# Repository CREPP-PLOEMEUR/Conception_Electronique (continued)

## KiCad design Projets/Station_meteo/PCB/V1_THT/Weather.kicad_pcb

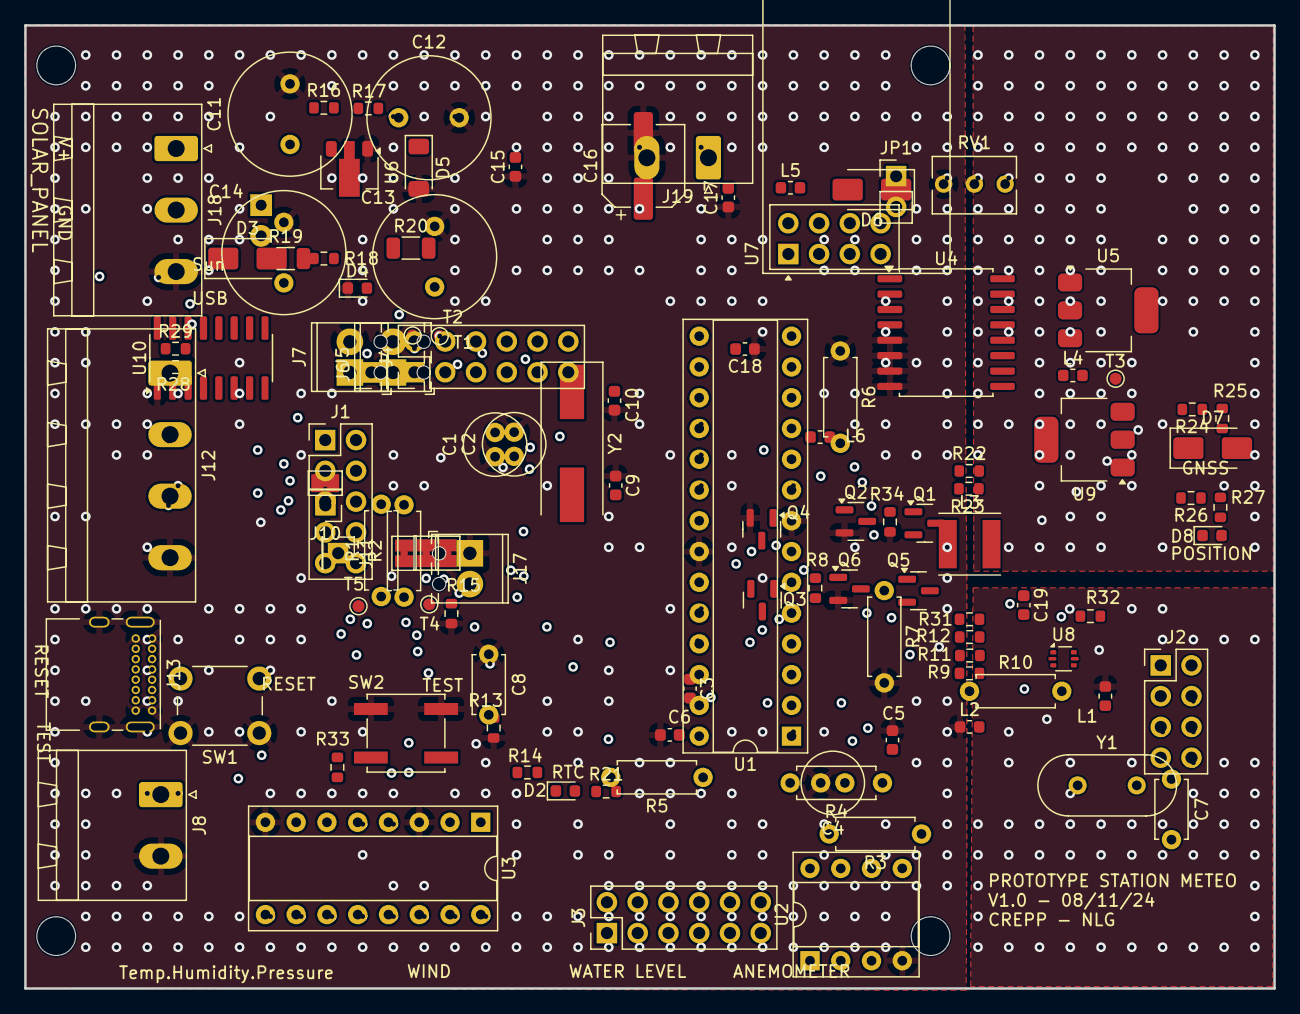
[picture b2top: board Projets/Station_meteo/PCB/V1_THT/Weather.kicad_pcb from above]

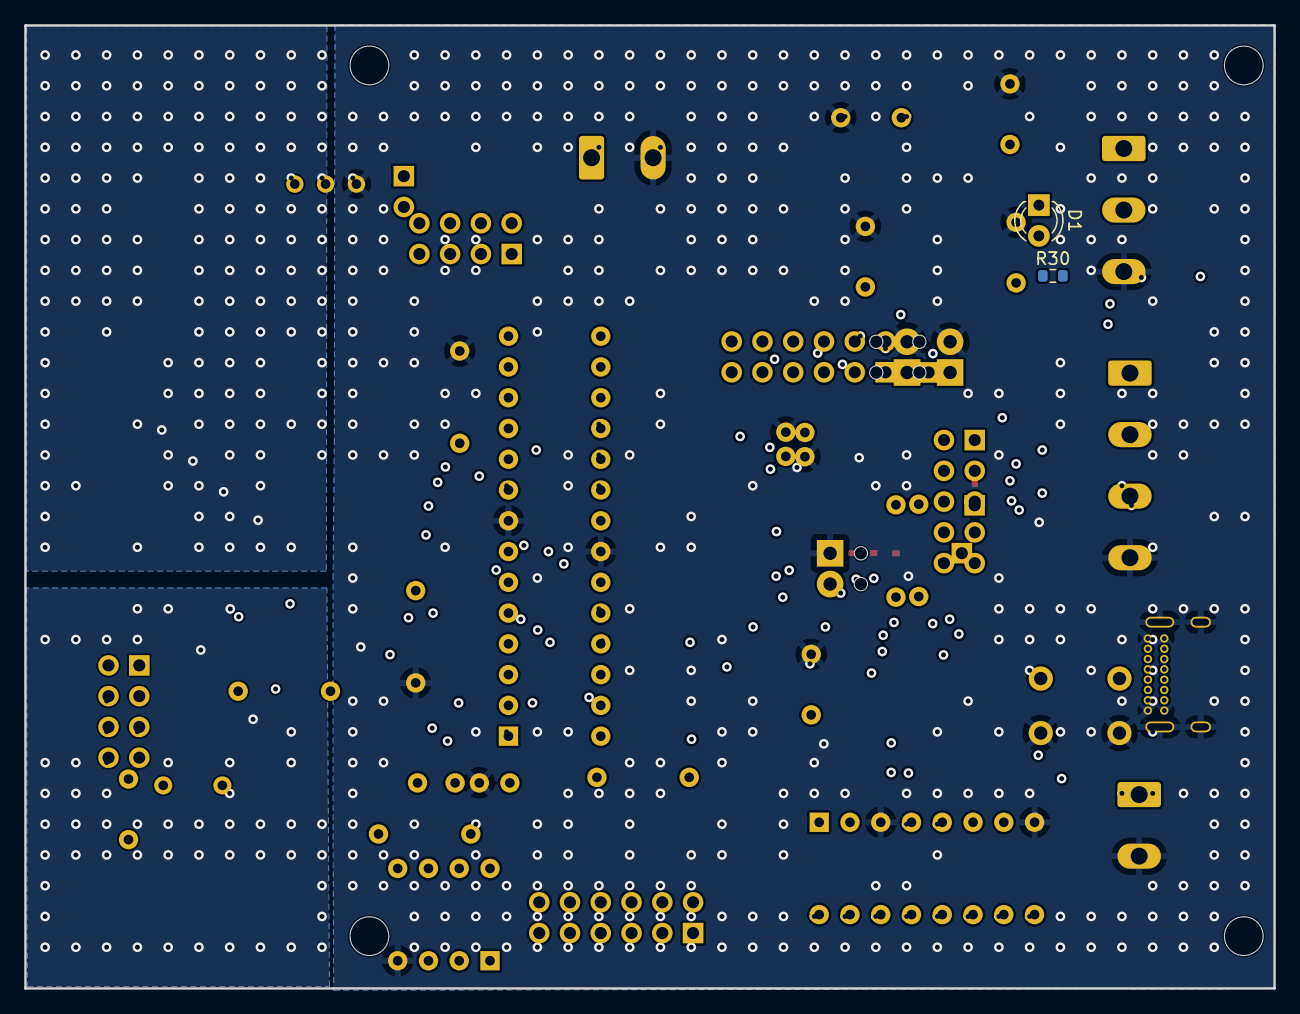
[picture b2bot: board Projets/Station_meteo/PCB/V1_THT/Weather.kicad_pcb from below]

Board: 2 copper layers, 103.1 x 79.5 mm, 117 parts (2 on the bottom side), 96 nets, no tracks yet.

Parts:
C1, C2, C4: 100nF; C_Radial_D5.0mm_H11.0mm_P2.00mm
C3, C5, C6, C19: 100nF; C_0603_1608Metric
C7, C8: 22pF; C_Disc_D4.7mm_W2.5mm_P5.00mm
C9, C10, C17, C18: 2.2uF; C_0603_1608Metric
C11, C12, C13, C14: 5F; C_Radial_D10.0mm_H20.0mm_P5.00mm
C15: 47uF; C_0603_1608Metric
C16: 100uF; CP_Elec_6.3x7.7
D1: LED; LED_D3.0mm
D2: LED; LED_0603_1608Metric
D3, D6, D7: SS24; D_SMA
D4: SUN; LED_0603_1608Metric
D5: D_Zener; D_MiniMELF
D8: LED_USB; LED_0603_1608Metric
H1, H2, H3, H4: MountingHole_Pad; MountingHole_3.2mm_M3
J1: Conn_02x05_Odd_Even; PinHeader_2x05_P2.54mm_Vertical
J2: Conn_02x04_Odd_Even; PinHeader_2x04_P2.54mm_Vertical
J3, J4: Conn_02x06_Odd_Even; PinHeader_2x06_P2.54mm_Vertical
J5: Wind; TerminalBlock_Phoenix_MPT-0,5-2-2.54_1x02_P2.54mm_Horizontal
J6: RAW_data_Wind; PinHeader_1x01_P2.54mm_Vertical
J7: USR_BTN; TerminalBlock_Phoenix_MPT-0,5-2-2.54_1x02_P2.54mm_Horizontal
J8: Panel; PhoenixContact_MSTBA_2,5_2-G-5,08_1x02_P5.08mm_Horizontal
J9, J14, J15, J16: SolderJumper_2_Bridged; SolderJumper-2_P1.3mm_Bridged_Pad1.0x1.5mm
J10, J11: Conn_01x01_Pin; PinHeader_1x01_P2.54mm_Vertical
J12: Screw_Terminal_01x04; PhoenixContact_MSTBA_2,5_4-G-5,08_1x04_P5.08mm_Horizontal
J13: USB_C_Receptacle_USB2.0_16P; USB_C_Receptacle_GCT_USB4085
J17: KF128-2.54_2P; TerminalBlock_Phoenix_MPT-0,5-2-2.54_1x02_P2.54mm_Horizontal
J18: Screw_Terminal_01x03; PhoenixContact_MSTBA_2,5_3-G-5,08_1x03_P5.08mm_Horizontal
J19: Water_Level; PhoenixContact_MSTBA_2,5_2-G-5,08_1x02_P5.08mm_Horizontal
JP1: Jumper; PinHeader_1x02_P2.54mm_Vertical
L1, L2, L4, L5, L6: MPZ1608S101ATAH0; L_0603_1608Metric
L3: 33uH; L_Taiyo-Yuden_NR-50xx
Q1, Q3, Q5: CJ3401; SOT-23
Q2, Q4, Q6: 2N7002H; SOT-23
R1, R2, R3, R4, R5, R6, R10: 10k; R_Axial_DIN0207_L6.3mm_D2.5mm_P7.62mm_Horizontal
R7: 270; R_Axial_DIN0207_L6.3mm_D2.5mm_P7.62mm_Horizontal
R8, R17, R21, R22, R23, R24, R25, R26, R27: 0; R_0603_1608Metric
R9, R18: 330; R_0603_1608Metric
R11, R29, R31, R33: 10k; R_0603_1608Metric
R12, R13, R14, R30, R32, R34: 100k; R_0603_1608Metric
R15: 390; R_0603_1608Metric
R16, R28: 270; R_0603_1608Metric
R19, R20: 100; R_1206_3216Metric
RV1: R_Potentiometer; Potentiometer_Bourns_3266Y_Vertical
SW1: SW_B; SW_PUSH_6mm_H8mm
SW2: PB_SMD_12V_50MA_6MM_6MM; SW_Push_1P1T_NO_CK_KSC7xxJ
T1, T2, T3, T4, T5: TP; TestPoint_Pad_D1.0mm
U1: ATmega328P-P; DIP-28_W7.62mm_Socket
U2: LM358; DIP-8_W7.62mm_Socket
U3: 74HC123; DIP-16_W7.62mm_Socket
U4: DS3231M; SOIC-16W_7.5x10.3mm_P1.27mm
U5: LM317_SOT-223; SOT-223-3_TabPin2
U6: BL8530; SOT-89-3
U7: NRF24L01_Breakout; nRF24L01_Breakout
U8: USBLC6-2P6; SOT-666
U9: AMS1117-3.3; SOT-223-3_TabPin2
U10: CH340G; SOIC-16_3.9x9.9mm_P1.27mm
Y1: 16MHz; Crystal_HC49-4H_Vertical
Y2: 12MHz; Crystal_SMD_HC49-SD

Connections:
/+3.3V_MCU: R10.1, R29.1
/+5V_USB: C17.2, D3.2 (A), J13.A4 (VBUS), J13.A9 (VBUS), J13.B4 (VBUS), J13.B9 (VBUS), U8.5 (VBUS), U9.3 (VI)
/Enable_GNSS: J2.8, Q4.1 (G), R32.1
/Enable_RF: J4.11, Q2.1 (G), R12.1
/Enable_Sensors: J2.6, Q6.1 (G), R34.1
/Interfaces/+3.3V: C6.1, D2.2 (A), J12.1, J18.1, Q5.3 (D), R30.1, U4.2 (VCC), U4.4 (~RST)
/Interfaces/Direction: J3.5, J18.2
/Interfaces/Water_Level: J4.7, J19.1, R30.2
/MCU/+VCC: C1.2, L5.2, U1.7 (VCC), U1.20 (AVCC)
/MCU/CLK: J1.2, R23.1
/MCU/MISO: J1.4, R21.1
/MCU/MOSI: J1.6, R22.1
/MCU/PB0: J2.1, U1.14 (PB0)
/MCU/PB2-D10~: J1.8, R24.1
/MCU/PC0-A0: J3.1, J9.2 (B)
/MCU/PC1-A1: J3.3, R13.1, R14.2
/MCU/PD3-D3-(INT1)~: J4.9, J17.2, R29.2, SW2.2 (B)
/MCU/PD7-D7: J2.4, R25.1
/MCU/RX: J4.3, J15.2 (B)
/MCU/SCL: J3.11, J12.2, U4.16 (SCL)
/MCU/SDA: J3.9, J12.3, U4.15 (SDA)
/MCU/TX: J4.5, J16.2 (B)
/MCU/XTAL1/PB6: C7.2, U1.9 (XTAL1/PB6), Y1.2
/MCU/XTAL2/PB7: C8.2, U1.10 (XTAL2/PB7), Y1.1
/NRF24/+3.3V: L6.1, L6.2, Q1.3 (D), U7.2 (VCC)
/Power/+3.3V: C16.1, D7.1 (K), J10.1, R20.1, U6.2 (OUT)
/Power/+3.3V_RF: J11.1, L4.1, L5.1, Q1.2 (S), Q3.2 (S), R11.2, R20.2, R31.2, T5.1
/Power/+3.3V_Sensors: L4.2, Q5.2 (S), R33.2
/Programming/+3.3V: C18.2, D8.2 (A), J14.2 (B), U9.2 (VO), U10.16 (VCC)
/Programming/D+: U8.1 (I/O1), U10.5 (UD+)
/Programming/D-: U8.3 (I/O2), U10.6 (UD-)
/RESET: C19.2, J4.1, J7.1, R10.2, SW1.2 (B)
/WIND/Vcc: C2.1, C4.1, R1.1, R2.1, RV1.1, U2.8 (V+), U3.16 (VCC)
/WIND/Wind_interrupt: JP1.1 (A), R5.2, R6.2, U2.1
GND: C1.1, C2.2, C4.2, C5.2, C6.2, C7.1, C8.1, C9.1, C10.1, C11.2, C12.2, C13.2, C14.2, C15.1, C16.2, C17.1, C18.1, D4.1 (K), D5.2 (A), J5.2, J7.2, J8.2, J12.4, J13.A1 (GND), J13.A12 (GND), J13.B1 (GND), J13.B12 (GND), J13.S1 (SHIELD), J17.1, J18.3, J19.2, L1.1, L2.1, Q2.2 (S), Q4.2 (S), Q6.2 (S), R6.1, R7.2, R12.2, R13.2, R15.1, R28.2, R32.2, R34.2, RV1.3, SW1.1 (A), SW2.1 (A), U1.8 (GND), U1.22 (GND), U2.4 (V-), U3.3 (Clr), U3.8 (GND), U4.5 (GND), U4.6 (GND), U4.7 (GND), U4.8 (GND), U4.9 (GND), U4.10 (GND), U4.11 (GND), U4.12 (GND), U4.13 (GND), U6.1 (GND), U8.2 (GND), U9.1 (GND), U10.1 (GND)
GND_RF: L1.2, U7.1 (GND)
unnamed: D1.2 (A), JP1.2 (B)
unnamed: D1.1 (K), R7.1
unnamed: D2.1 (K), R9.1
unnamed: C9.2, D3.1 (K), J8.1, R14.1, T2.1, U5.3 (VI)
unnamed: D4.2 (A), R18.1
unnamed: C10.2, D5.1 (K), R16.2, R17.2, R19.1, T3.1, U5.2 (VO)
unnamed: D6.2 (A), R19.2
unnamed: C11.1, C12.1, C13.1, C14.1, C15.2, D6.1 (K), J9.1 (A), L3.1, T4.1
unnamed: D7.2 (A), L3.2, U6.3 (LX)
unnamed: D8.1 (K), R28.1
unnamed: J1.1, U1.19 (PB5)
unnamed: J1.3, U1.18 (PB4)
unnamed: J1.5, U1.17 (PB3)
unnamed: J1.7, U1.16 (PB2)
unnamed: J1.9, U1.15 (PB1)
unnamed: J2.3, U1.13 (PD7)
unnamed: J2.5, U1.12 (PD6)
unnamed: J2.7, U1.11 (PD5)
unnamed: J3.2, U1.23 (PC0)
unnamed: J3.4, U1.24 (PC1)
unnamed: J3.6, U1.25 (PC2)
unnamed: J3.8, U1.26 (PC3)
unnamed: J3.10, U1.27 (PC4)
unnamed: J3.12, U1.28 (PC5)
unnamed: J4.2, U1.1 (~RESET/PC6)
unnamed: J4.4, U1.2 (PD0)
unnamed: J4.6, U1.3 (PD1)
unnamed: J4.8, U1.4 (PD2)
unnamed: J4.10, U1.5 (PD3)
unnamed: J4.12, U1.6 (PD4)
unnamed: J5.1, J6.1, R1.2, U3.2 (B)
unnamed: J13.A6 (D+), J13.B6 (D+), R27.1
unnamed: J13.A7 (D-), J13.B7 (D-), R26.1
unnamed: J14.1 (A), U10.4 (V3)
unnamed: J15.1 (A), U10.2 (TXD)
unnamed: J16.1 (A), U10.3 (RXD)
unnamed: Q1.1 (G), Q2.3 (D), R11.1
unnamed: Q3.1 (G), Q4.3 (D), R31.1
unnamed: Q5.1 (G), Q6.3 (D), R33.1
unnamed: R8.2, R9.2
unnamed: R17.1, R18.2
unnamed: R26.2, U8.4 (I/O2)
unnamed: R27.2, U8.6 (I/O1)
unnamed: R4.2, R5.1, U2.3 (+)
unnamed: RV1.2, U2.2 (-)
unnamed: C5.1, R3.2, U2.5 (+)
unnamed: R4.1, U2.6 (-), U2.7
unnamed: C3.2, U3.14 (Cext)
unnamed: R3.1, U3.13 (Q)
unnamed: C3.1, R2.2, U3.15 (RCext)
unnamed: R8.1, T1.1, U4.3 (~INT/SQW)
unnamed: R15.2, R16.1, U5.1 (ADJ)
unnamed: R25.2, U7.3 (CE)
unnamed: R22.2, U7.7 (MISO)
unnamed: R21.2, U7.6 (MOSI)
unnamed: R23.2, U7.5 (SCK)
unnamed: R24.2, U7.4 (~CSN)
unnamed: U10.7 (XI), Y2.1
unnamed: U10.8 (XO), Y2.2
unnamed: C19.1, U10.13 (~DTR)

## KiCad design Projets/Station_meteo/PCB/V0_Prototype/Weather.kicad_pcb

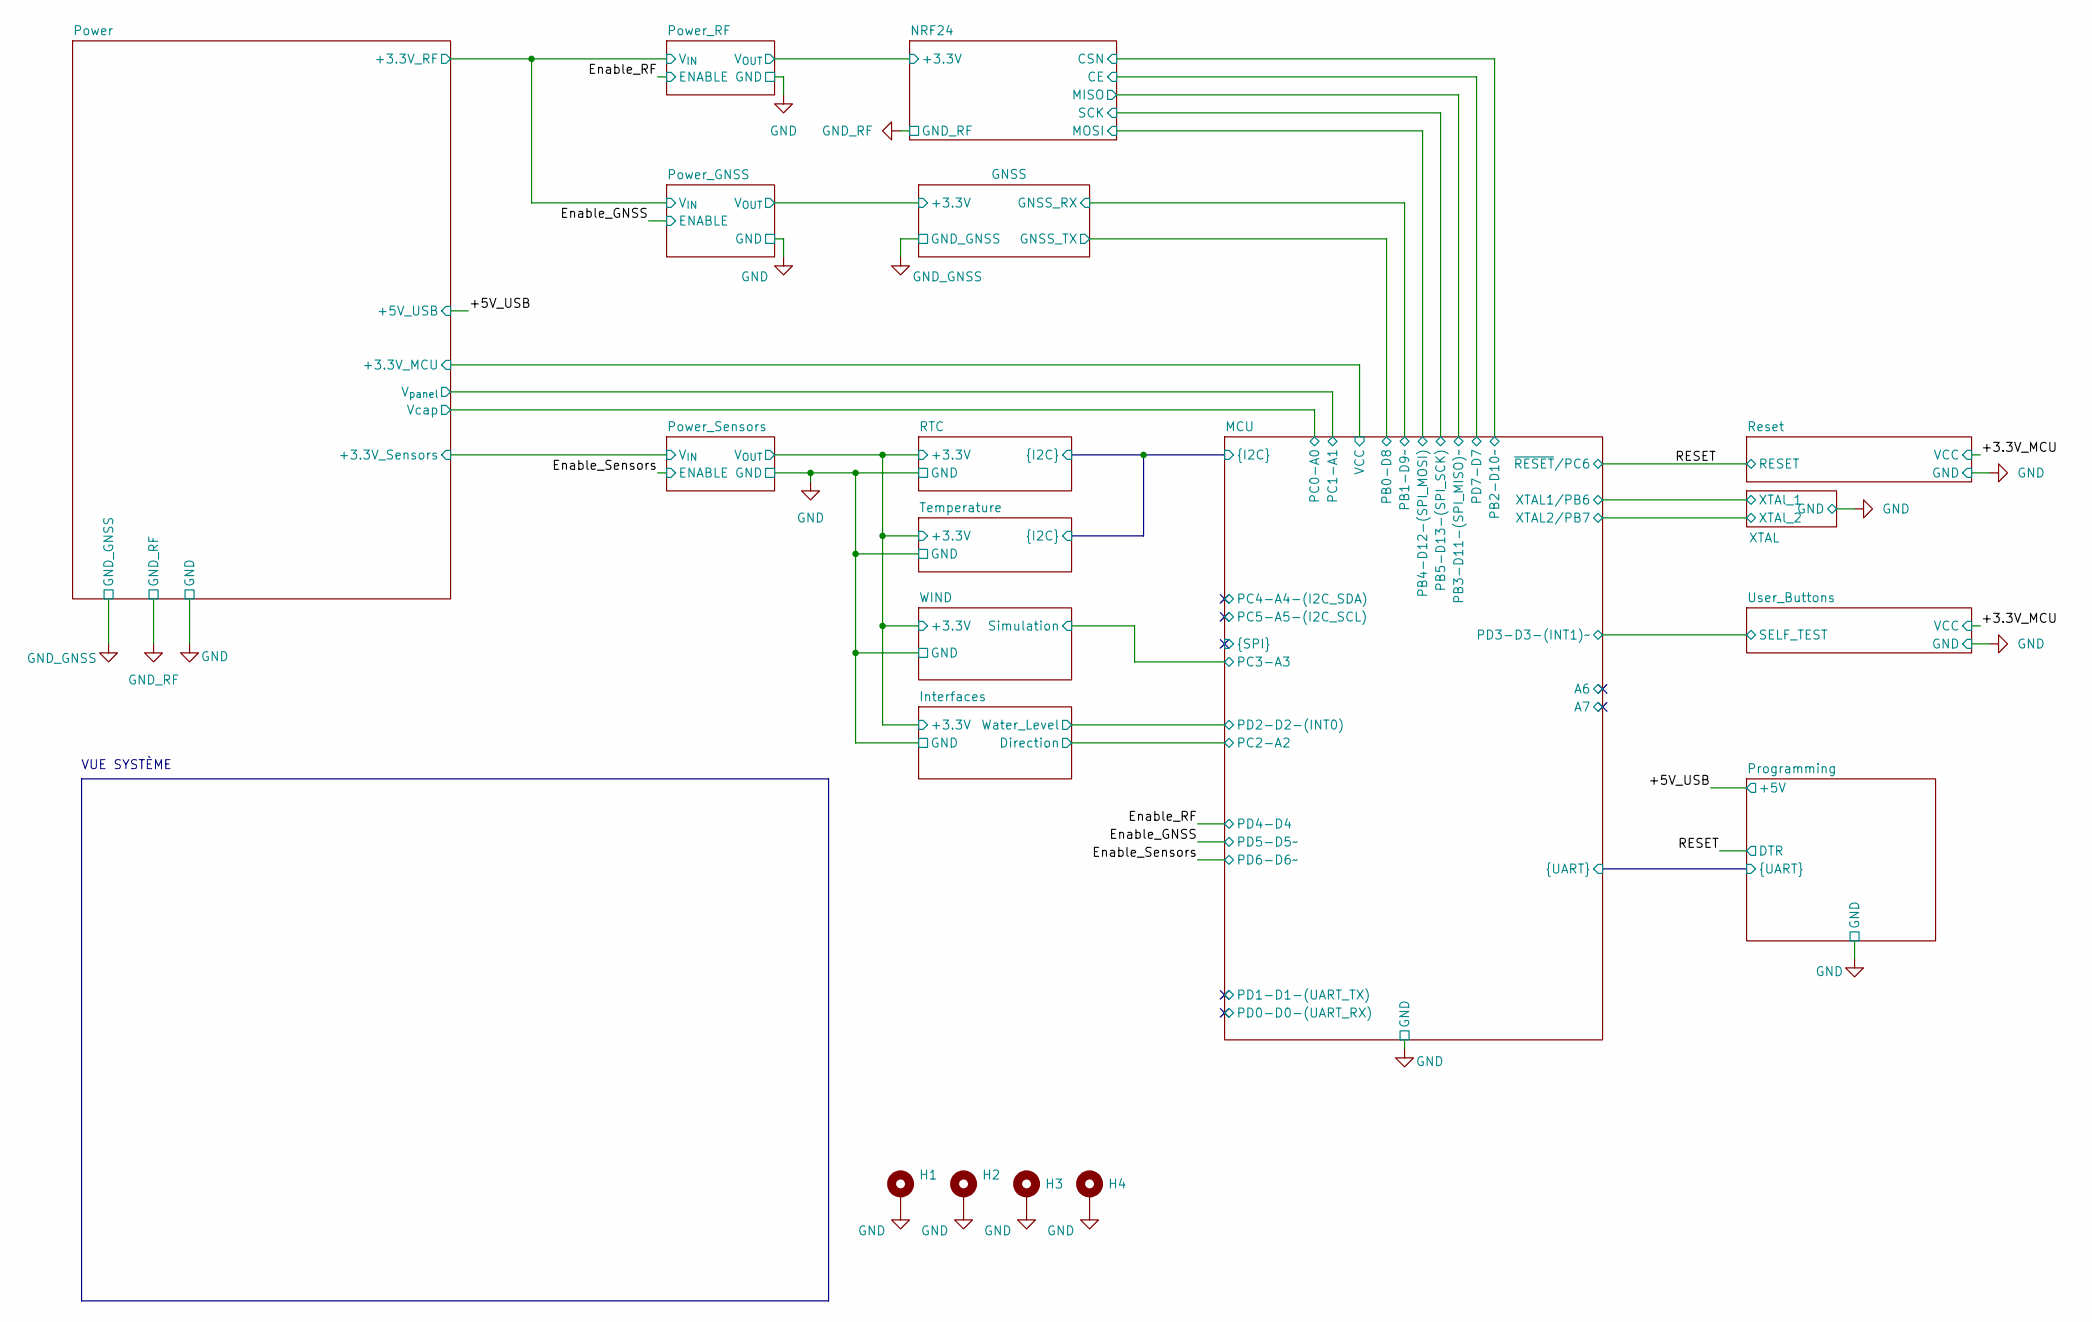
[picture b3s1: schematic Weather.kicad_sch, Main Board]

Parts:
H1, H2, H3, H4: MountingHole_Pad; MountingHole_3.2mm_M3

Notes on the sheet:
VUE SYSTÈME

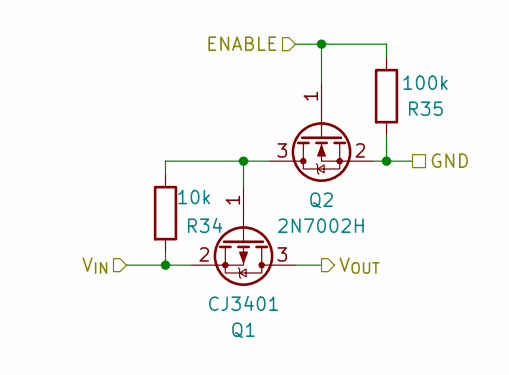
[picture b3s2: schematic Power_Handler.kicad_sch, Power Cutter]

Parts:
Q1: CJ3401; SOT-23
Q2: 2N7002H; SOT-23
R34: 10k; R_0603_1608Metric
R35: 100k; R_0603_1608Metric

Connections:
/Enable_GNSS: Q2.1 (G), R35.1; also elsewhere on the board
/GNSS/+3.3V: Q1.3 (D); also elsewhere on the board
/Power/+3.3V_RF: Q1.2 (S), R34.2; also elsewhere on the board
GND: Q2.2 (S), R35.2; also elsewhere on the board
unnamed: Q1.1 (G), Q2.3 (D), R34.1

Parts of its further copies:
Q3, Q5: CJ3401; SOT-23
Q4, Q6: 2N7002H; SOT-23
R7, R36: 10k; R_0603_1608Metric
R8, R37: 100k; R_0603_1608Metric

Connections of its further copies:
/Enable_RF: Q6.1 (G), R8.1; also elsewhere on the board
/Enable_Sensors: Q4.1 (G), R37.1; also elsewhere on the board
/Interfaces/+3.3V: Q3.3 (D); also elsewhere on the board
/NRF24/+3.3V: Q5.3 (D); also elsewhere on the board
/Power/+3.3V_RF: Q5.2 (S), R7.2; also elsewhere on the board
/Power/+3.3V_Sensors: Q3.2 (S), R36.2; also elsewhere on the board
GND: Q4.2 (S), Q6.2 (S), R8.2, R37.2; also elsewhere on the board
unnamed: Q3.1 (G), Q4.3 (D), R36.1
unnamed: Q5.1 (G), Q6.3 (D), R7.1

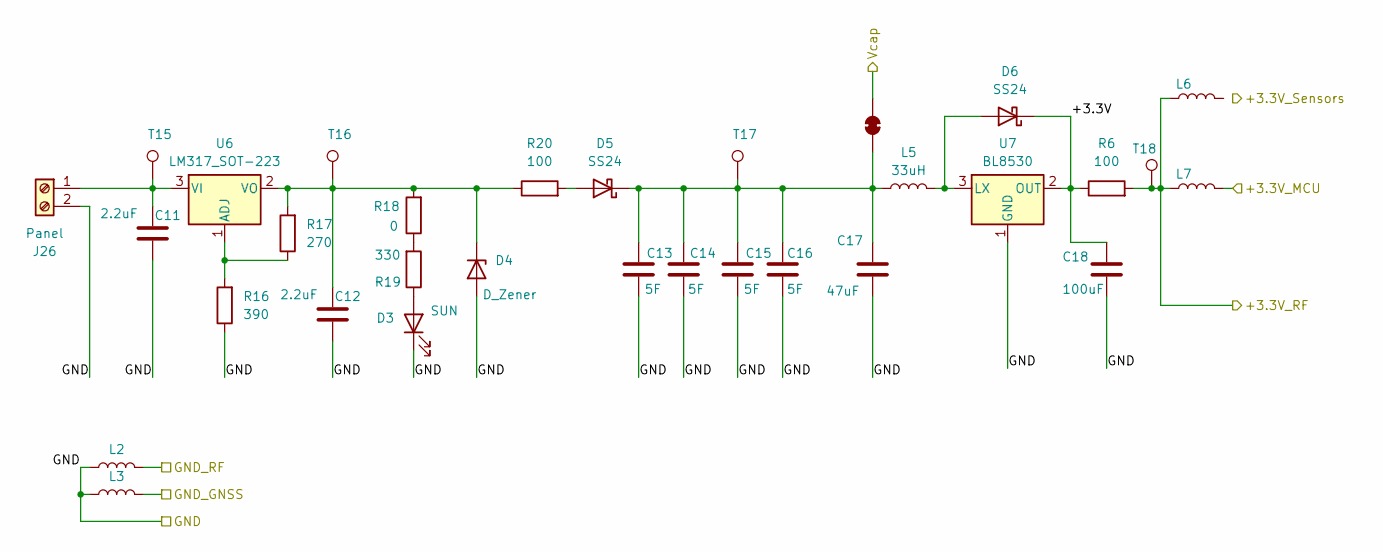
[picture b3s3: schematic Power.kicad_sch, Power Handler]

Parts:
C11, C12: 2.2uF; C_0603_1608Metric
C13, C14, C15, C16: 5F; C_Radial_D10.0mm_H20.0mm_P5.00mm
C17: 47uF; C_0603_1608Metric
C18: 100uF; CP_Elec_6.3x7.7
D3: SUN; LED_0603_1608Metric
D4: D_Zener; D_MiniMELF
D5, D6: SS24; D_SMA
J26: Panel; PhoenixContact_MSTBA_2,5_2-G-5,08_1x02_P5.08mm_Horizontal
J39: SolderJumper_2_Bridged; SolderJumper-2_P1.3mm_Bridged_Pad1.0x1.5mm
L2, L3, L6, L7: MPZ1608S101ATAH0; L_0603_1608Metric
L5: 33uH; L_Taiyo-Yuden_NR-50xx
R6, R20: 100; R_1206_3216Metric
R16: 390; R_0603_1608Metric
R17: 270; R_0603_1608Metric
R18: 0; R_0603_1608Metric
R19: 330; R_0603_1608Metric
T15, T16, T17, T18: TP; TestPoint_Pad_D1.0mm
U6: LM317_SOT-223; SOT-223-3_TabPin2
U7: BL8530; SOT-89-3

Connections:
/MCU/+VCC: L7.2; also elsewhere on the board
/MCU/PC0-A0: J39.2 (B); also elsewhere on the board
/Power/+3.3V: C18.1, D6.1 (K), R6.1, U7.2 (OUT); also elsewhere on the board
/Power/+3.3V_RF: L6.1, L7.1, R6.2, T18.1; also elsewhere on the board
/Power/+3.3V_Sensors: L6.2; also elsewhere on the board
GND: C11.1, C12.1, C13.2, C14.2, C15.2, C16.2, C17.1, C18.2, D3.1 (K), D4.2 (A), J26.2, L2.1, L3.1, R16.1, U7.1 (GND); also elsewhere on the board
GND_GNSS: L3.2; also elsewhere on the board
GND_RF: L2.2; also elsewhere on the board
unnamed 44: C11.2, J26.1, T15.1, U6.3 (VI); also elsewhere on the board
unnamed: D3.2 (A), R19.1
unnamed: C12.2, D4.1 (K), R17.2, R18.2, R20.1, T16.1, U6.2 (VO)
unnamed: D5.2 (A), R20.2
unnamed: C13.1, C14.1, C15.1, C16.1, C17.2, D5.1 (K), J39.1 (A), L5.1, T17.1
unnamed: D6.2 (A), L5.2, U7.3 (LX)
unnamed: R18.1, R19.2
unnamed: R16.2, R17.1, U6.1 (ADJ)

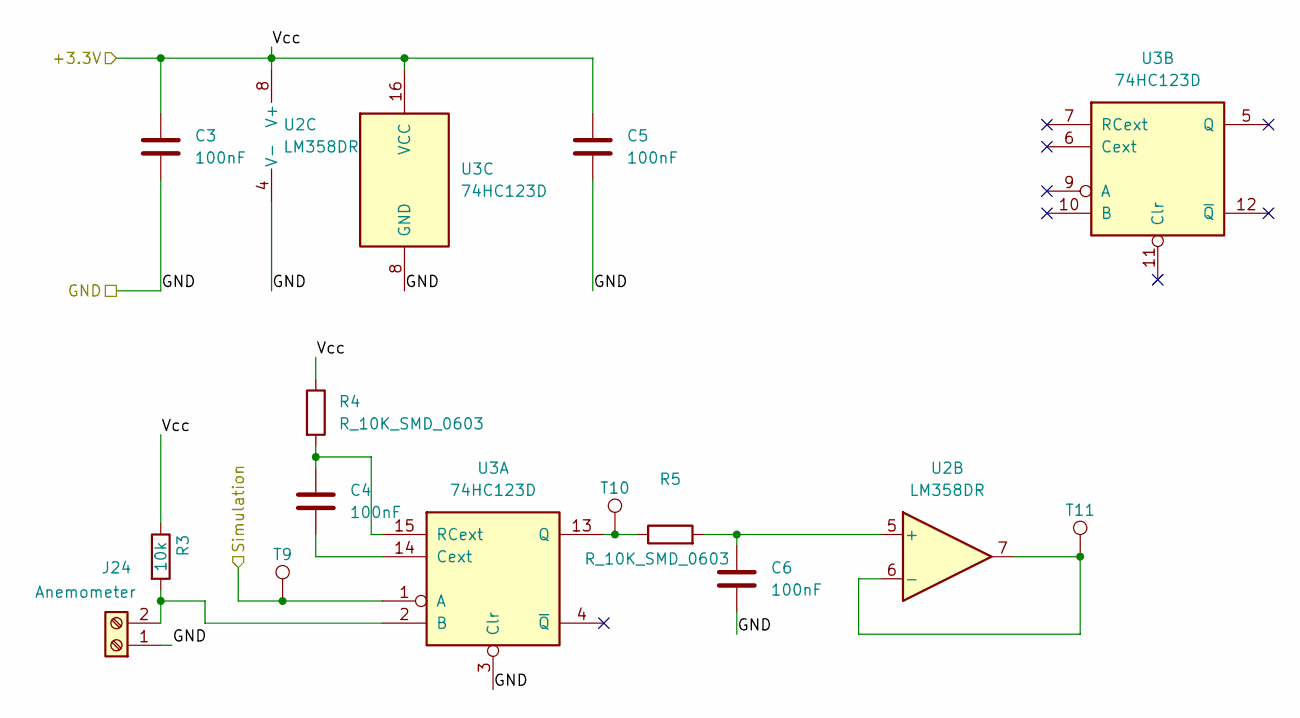
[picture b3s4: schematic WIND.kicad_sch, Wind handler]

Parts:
C3, C4, C5, C6: 100nF; C_0603_1608Metric
J24: Anemometer; PhoenixContact_MSTBA_2,5_2-G-5,08_1x02_P5.08mm_Horizontal
R3: 10k; R_0603_1608Metric
R4, R5: R_10K_SMD_0603; R_0603_1608Metric
T9, T10, T11: TP; TestPoint_Pad_D1.0mm
U2: LM358DR; TSSOP-8_4.4x3mm_P0.65mm
U3: 74HC123D; SOIC-16W_5.3x10.2mm_P1.27mm

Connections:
/Interfaces/+3.3V: C3.1, C5.1, R3.1, R4.1, U2.8 (V+), U3.16 (VCC); also elsewhere on the board
/MCU/PC3-A3: T9.1, U3.1 (A); also elsewhere on the board
GND: C3.2, C5.2, C6.2, J24.1, U2.4 (V-), U3.3 (Clr), U3.8 (GND); also elsewhere on the board
unnamed: J24.2, R3.2, U3.2 (B)
unnamed: C6.1, R5.2, U2.5 (+)
unnamed: T11.1, U2.6 (-), U2.7
unnamed: C4.2, U3.14 (Cext)
unnamed: R5.1, T10.1, U3.13 (Q)
unnamed: C4.1, R4.2, U3.15 (RCext)

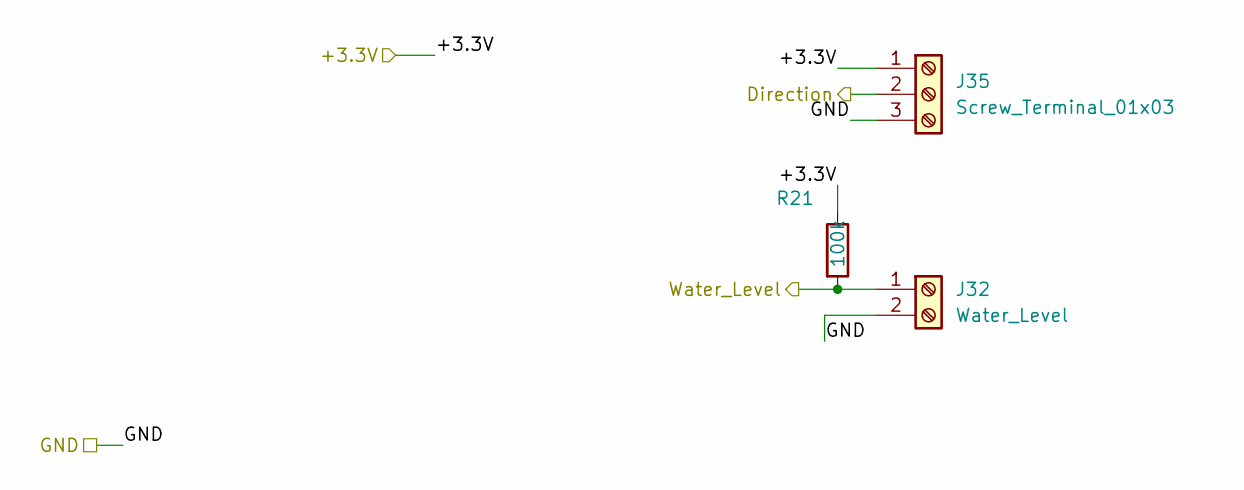
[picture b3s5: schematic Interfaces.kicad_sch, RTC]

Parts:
J32: Water_Level; PhoenixContact_MSTBA_2,5_2-G-5,08_1x02_P5.08mm_Horizontal
J35: Screw_Terminal_01x03; PhoenixContact_MSTBA_2,5_3-G-5,08_1x03_P5.08mm_Horizontal
R21: 100k; R_0603_1608Metric

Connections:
/Interfaces/+3.3V: J35.1, R21.1; also elsewhere on the board
/Interfaces/Direction: J35.2; also elsewhere on the board
/Interfaces/Water_Level: J32.1, R21.2; also elsewhere on the board
GND: J32.2, J35.3; also elsewhere on the board

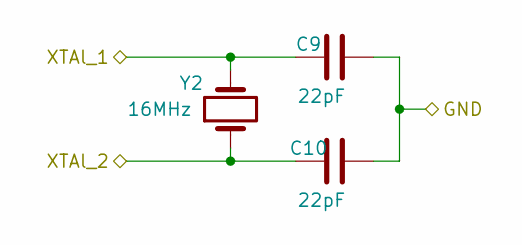
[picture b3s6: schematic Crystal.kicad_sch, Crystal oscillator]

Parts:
C9, C10: 22pF; C_0603_1608Metric
Y2: 16MHz; Crystal_SMD_HC49-SD

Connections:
/MCU/XTAL1/PB6: C9.2, Y2.2; also elsewhere on the board
/MCU/XTAL2/PB7: C10.2, Y2.1; also elsewhere on the board
GND: C9.1, C10.1; also elsewhere on the board

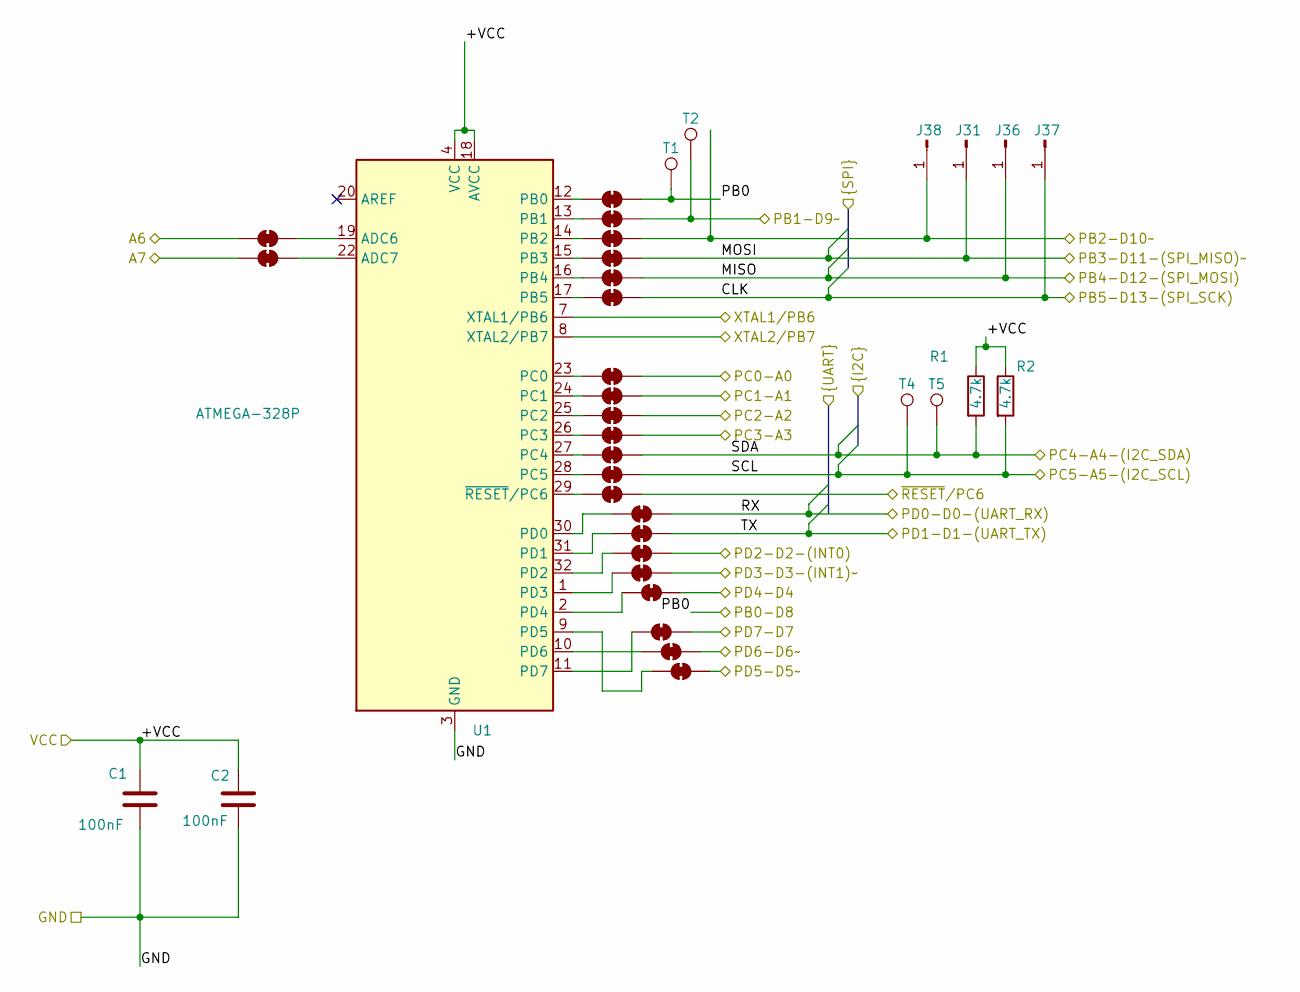
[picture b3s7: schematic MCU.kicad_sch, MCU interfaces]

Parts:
C1, C2: 100nF; C_0603_1608Metric
J1, J2, J3, J4, J5, J6, J7, J8, J9, J10, J11, J12, J13, J14, J15, J16, J17, J18, J19, J20, J21, J22, J23: SolderJumper_2_Bridged; SolderJumper-2_P1.3mm_Bridged_Pad1.0x1.5mm
J31, J36, J37, J38: Conn_01x01_Pin; PinHeader_1x01_P2.54mm_Vertical
R1, R2: 4.7k; R_0603_1608Metric
T1, T2, T4, T5: TP; TestPoint_Pad_D1.0mm
U1: ATMEGA-328P; TQFP-32_7x7mm_P0.8mm

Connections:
/Enable_GNSS: J23.2 (B); also elsewhere on the board
/Enable_RF: J20.2 (B); also elsewhere on the board
/Enable_Sensors: J22.2 (B); also elsewhere on the board
/GNSS/GNSS_RX: J4.2 (B), T2.1; also elsewhere on the board
/Interfaces/Direction: J11.2 (B); also elsewhere on the board
/Interfaces/Water_Level: J18.2 (B); also elsewhere on the board
/MCU/+VCC: C1.2, C2.2, R1.1, R2.1, U1.4 (VCC), U1.6 (VCC), U1.18 (AVCC); also elsewhere on the board
/MCU/A6: J1.1 (A)
/MCU/A7: J2.1 (A)
/MCU/CLK: J8.2 (B), J37.1; also elsewhere on the board
/MCU/MISO: J7.2 (B), J36.1; also elsewhere on the board
/MCU/MOSI: J6.2 (B), J31.1; also elsewhere on the board
/MCU/PB0: J3.2 (B), T1.1; also elsewhere on the board
/MCU/PB2-D10~: J5.2 (B), J38.1; also elsewhere on the board
/MCU/PC0-A0: J9.2 (B); also elsewhere on the board
/MCU/PC1-A1: J10.2 (B); also elsewhere on the board
/MCU/PC3-A3: J12.2 (B); also elsewhere on the board
/MCU/PD3-D3-(INT1)~: J19.2 (B); also elsewhere on the board
/MCU/PD7-D7: J21.2 (B); also elsewhere on the board
/MCU/RX: J16.2 (B); also elsewhere on the board
/MCU/SCL: J14.2 (B), R2.2, T4.1; also elsewhere on the board
/MCU/SDA: J13.2 (B), R1.2, T5.1; also elsewhere on the board
/MCU/TX: J17.2 (B); also elsewhere on the board
/MCU/XTAL1/PB6: U1.7 (XTAL1/PB6); also elsewhere on the board
/MCU/XTAL2/PB7: U1.8 (XTAL2/PB7); also elsewhere on the board
/RESET: J15.2 (B); also elsewhere on the board
GND: C1.1, C2.1, U1.3 (GND), U1.5 (GND), U1.21 (GND); also elsewhere on the board
unnamed: J1.2 (B), U1.19 (ADC6)
unnamed: J2.2 (B), U1.22 (ADC7)
unnamed: J3.1 (A), U1.12 (PB0)
unnamed: J4.1 (A), U1.13 (PB1)
unnamed: J5.1 (A), U1.14 (PB2)
unnamed: J6.1 (A), U1.15 (PB3)
unnamed: J7.1 (A), U1.16 (PB4)
unnamed: J8.1 (A), U1.17 (PB5)
unnamed: J9.1 (A), U1.23 (PC0)
unnamed: J10.1 (A), U1.24 (PC1)
unnamed: J11.1 (A), U1.25 (PC2)
unnamed: J12.1 (A), U1.26 (PC3)
unnamed: J13.1 (A), U1.27 (PC4)
unnamed: J14.1 (A), U1.28 (PC5)
unnamed: J15.1 (A), U1.29 (~RESET/PC6)
unnamed: J16.1 (A), U1.30 (PD0)
unnamed: J17.1 (A), U1.31 (PD1)
unnamed: J18.1 (A), U1.32 (PD2)
unnamed: J19.1 (A), U1.1 (PD3)
unnamed: J20.1 (A), U1.2 (PD4)
unnamed: J21.1 (A), U1.11 (PD7)
unnamed: J22.1 (A), U1.10 (PD6)
unnamed: J23.1 (A), U1.9 (PD5)

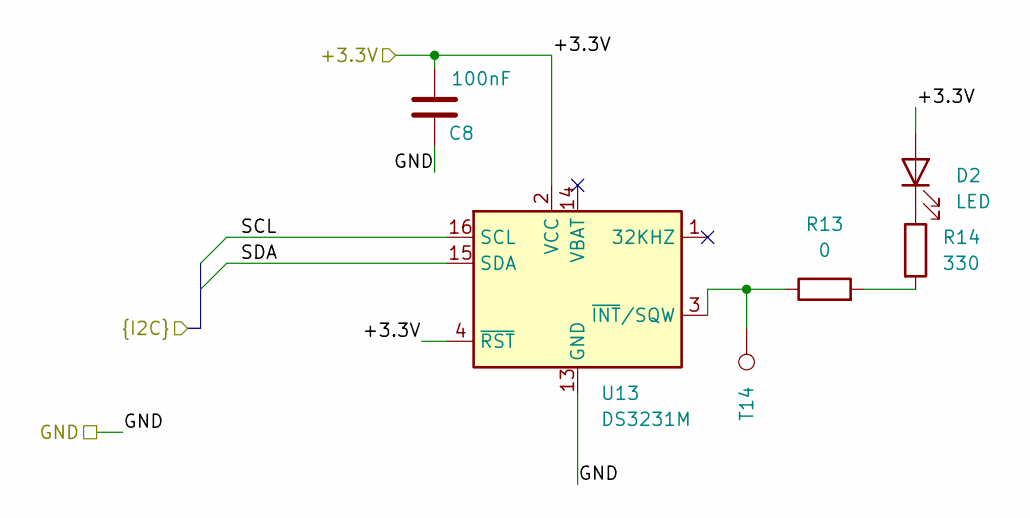
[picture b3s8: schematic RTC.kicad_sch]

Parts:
C8: 100nF; C_0603_1608Metric
D2: LED; LED_0603_1608Metric
R13: 0; R_0603_1608Metric
R14: 330; R_0603_1608Metric
T14: TP; TestPoint_Pad_D1.0mm
U13: DS3231M; SOIC-16W_7.5x10.3mm_P1.27mm

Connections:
/Interfaces/+3.3V: C8.1, D2.2 (A), U13.2 (VCC), U13.4 (~RST); also elsewhere on the board
/MCU/SCL: U13.16 (SCL); also elsewhere on the board
/MCU/SDA: U13.15 (SDA); also elsewhere on the board
GND: C8.2, U13.5 (GND), U13.6 (GND), U13.7 (GND), U13.8 (GND), U13.9 (GND), U13.10 (GND), U13.11 (GND), U13.12 (GND), U13.13 (GND); also elsewhere on the board
unnamed: D2.1 (K), R14.1
unnamed: R13.2, R14.2
unnamed: R13.1, T14.1, U13.3 (~INT/SQW)

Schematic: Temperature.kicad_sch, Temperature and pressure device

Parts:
J33: Screw_Terminal_01x04; PhoenixContact_MSTBA_2,5_4-G-5,08_1x04_P5.08mm_Horizontal

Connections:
/Interfaces/+3.3V: J33.1; also elsewhere on the board
/MCU/SCL: J33.2; also elsewhere on the board
/MCU/SDA: J33.3; also elsewhere on the board
GND: J33.4; also elsewhere on the board

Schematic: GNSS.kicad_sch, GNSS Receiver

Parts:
AE1: Internal_antenna; MountingHole_2.2mm_M2_DIN965_Pad
C26: 100nF; C_0603_1608Metric
C27: 120pF; C_0603_1608Metric
D7: GNSS; LED_0603_1608Metric
D8: POS_ENABLE; LED_0603_1608Metric
L8: MPZ1608S101ATAH0; L_0603_1608Metric
R22, R23, R24, R26: 0; R_0603_1608Metric
R25, R27: 330; R_0603_1608Metric
T19, T20: TP; TestPoint_Pad_D1.0mm
U9: NEO-M8M; ublox_NEO

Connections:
/GNSS/+3.3V: C26.2, L8.1, L8.2, R24.2, T20.1, U9.8 (~RESET), U9.23 (VCC); also elsewhere on the board
/GNSS/GNSS_RX: R23.1; also elsewhere on the board
/MCU/PB0: R22.1; also elsewhere on the board
GND_GNSS: C26.1, D7.1 (K), D8.1 (K), U9.10 (GND), U9.12 (GND), U9.13 (GND), U9.24 (GND); also elsewhere on the board
unnamed: AE1.1 (A), C27.1
unnamed: D7.2 (A), R25.1
unnamed: D8.2 (A), R27.1
unnamed: R24.1, R25.2
unnamed: R26.1, R27.2
unnamed: T19.1, U9.2 (D_SEL)
unnamed: C27.2, U9.11 (RF_IN)
unnamed: R23.2, U9.21 (RXD/SPI_MOSI)
unnamed: R26.2, U9.3 (TIMEPULSE)
unnamed: R22.2, U9.20 (TXD/SPI_MISO)

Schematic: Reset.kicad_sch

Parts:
J25: KF128-2.54_2P; TerminalBlock_Phoenix_MPT-0,5-2-2.54_1x02_P2.54mm_Horizontal
R15: 10k; R_0603_1608Metric
SW1: PB_SMD_12V_50MA_6MM_6MM; SW_Push_1P1T_NO_CK_KSC7xxJ

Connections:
/+3.3V_MCU: R15.1; also elsewhere on the board
/RESET: J25.1, R15.2, SW1.2 (B); also elsewhere on the board
GND: J25.2, SW1.1 (A); also elsewhere on the board

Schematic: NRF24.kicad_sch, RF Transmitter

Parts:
C19: 4.7uF; C_0603_1608Metric
C20, C21, C22: 100nF; C_0603_1608Metric
C23: 2.2nF; C_0603_1608Metric
C24: 4.7pF; C_0603_1608Metric
C25: 1.5pF; C_0603_1608Metric
J27: 132415; SMA_Molex_73251-1153_EdgeMount_Horizontal
L1, L10, L11: 8.2nH; L_0603_1608Metric
L9: MPZ1608S101ATAH0; L_0603_1608Metric
R9, R10, R11, R12, R31: 0; R_0603_1608Metric
R32: 22k; R_0603_1608Metric
U8: NRF24L01; QFN-20-1EP_4x4mm_P0.5mm_EP2.5x2.5mm

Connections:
/MCU/CLK: R11.1; also elsewhere on the board
/MCU/MISO: R9.1; also elsewhere on the board
/MCU/MOSI: R10.1; also elsewhere on the board
/MCU/PB2-D10~: R12.1; also elsewhere on the board
/MCU/PD7-D7: R31.1; also elsewhere on the board
/NRF24/+3.3V: C19.1, C20.1, C21.1, C22.1, L9.1, L9.2, U8.7 (VDD), U8.15 (VDD), U8.18 (VDD); also elsewhere on the board
/NRF24/XTAL1/XTAl_1: U8.10 (XC1); also elsewhere on the board
/NRF24/XTAL1/XTAl_2: U8.9 (XC2); also elsewhere on the board
GND_RF: C19.2, C20.2, C21.2, C22.2, C23.2, C24.2, J27.2 (Ext), R32.1, U8.8 (VSS), U8.14 (VSS), U8.17 (VSS), U8.20 (VSS); also elsewhere on the board
unnamed: C25.1, L10.2
unnamed: C25.2, J27.1 (In)
unnamed: L1.2, L10.1, L11.1, U8.12 (ANT1)
unnamed: L11.2, U8.13 (ANT2)
unnamed: R31.2, U8.1 (CE)
unnamed: R12.2, U8.2 (CSN)
unnamed: R32.2, U8.16 (IREF)
unnamed: R10.2, U8.5 (MISO)
unnamed: R9.2, U8.4 (MOSI)
unnamed: R11.2, U8.3 (SCK)
unnamed: C23.1, C24.1, L1.1, U8.11 (VDD_PA)

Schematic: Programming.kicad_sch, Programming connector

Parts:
C28, C29: 2.2uF; C_0603_1608Metric
C30: 100nF; C_0603_1608Metric
D9: LED_USB; LED_0603_1608Metric
J28, J34, J40: SolderJumper_2_Bridged; SolderJumper-2_P1.3mm_Bridged_Pad1.0x1.5mm
J29: USB_C_Receptacle_USB2.0_16P; USB_C_Receptacle_GCT_USB4085
R28, R29: 0; R_0603_1608Metric
R30: 270; R_0603_1608Metric
U10: USBLC6-2P6; SOT-666
U11: CH340G; SOIC-16_3.9x9.9mm_P1.27mm
U12: AMS1117-3.3; SOT-223-3_TabPin2
Y3: 12MHz; Crystal_SMD_HC49-SD

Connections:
/+5V_USB: C28.2, J29.A4 (VBUS), J29.A9 (VBUS), J29.B4 (VBUS), J29.B9 (VBUS), U10.5 (VBUS), U12.3 (VI); also elsewhere on the board
/MCU/RX: J28.2 (B); also elsewhere on the board
/MCU/TX: J34.2 (B); also elsewhere on the board
/Programming/+3.3V: C29.2, D9.2 (A), J40.2 (B), U11.16 (VCC), U12.2 (VO)
/Programming/D+: U10.1 (I/O1), U11.5 (UD+)
/Programming/D-: U10.3 (I/O2), U11.6 (UD-)
/RESET: C30.2; also elsewhere on the board
GND: C28.1, C29.1, J29.A1 (GND), J29.A12 (GND), J29.B1 (GND), J29.B12 (GND), J29.S1 (SHIELD), R30.2, U10.2 (GND), U11.1 (GND), U12.1 (GND); also elsewhere on the board
unnamed: D9.1 (K), R30.1
unnamed: J28.1 (A), U11.2 (TXD)
unnamed: J29.A6 (D+), J29.B6 (D+), R29.1
unnamed: J29.A7 (D-), J29.B7 (D-), R28.1
unnamed: J34.1 (A), U11.3 (RXD)
unnamed: J40.1 (A), U11.4 (V3)
unnamed: R28.2, U10.4 (I/O2)
unnamed: R29.2, U10.6 (I/O1)
unnamed: U11.7 (XI), Y3.1
unnamed: U11.8 (XO), Y3.2
unnamed: C30.1, U11.13 (~DTR)
